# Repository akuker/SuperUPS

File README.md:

# Supercapacitor UPS board for Raspberry Pi

This is a fork of the original Supercapacitor UPS board for a Raspberry Pi by Scott Baker, http://www.smbaker.com/

This fork is intended to improve producability, documentation and provide tighter integration with the RaSCSI project. This project does NOT require a RaSCSI to function.

See [SETUP.md](SETUP.md) for setup instructions

## Very early 3D renderings

## Why not other Supercapacitor designs?

Most of the existing Raspberry Pi UPS designs rely on GPIO pins to alert the Raspberry Pi of a power loss. The RaSCSI design makes heavy usage of the GPIO pins, so there are not sufficient spare to allow this. This design will utilize a microcontroller to manage the power and allow the Rapsberry Pi to read the status through I2C.

# Purpose

These boards are supercapacitor-based uninterruptable power supplies. The supercapacitor charges when power is applied, then when the power supply is terminated, the supercapacitor will operate the device long enough for it to shut down safely.

# Design - 12V board (5v output)

The 12V board uses five 2.7V supercapacitors in series, with 2.7V shunt regulators to ensure that no single capacitor is charged to more than 2.5 volts. A 3W resistor is used to limit the current that charges the capacitors. A jumper is provided to allow the capacitors to be rapid discharged. A mosfet is added to allow the load to be turned on/off.

Note: Scott Baker's original design also included a version of the UPS board that took a 5v input. This fork is focusing on the 12v version and will not include the 5v input version.

# Microcontroller manager

~~An ATTiny85 is used as the controller for the UPS.~~ *Now a STM8 due to the parts shortages.* The microcontroller monitors the battery voltage and the incoming voltage, and switches the load on and off. The microcontroller supports I2C and can be interfaced directly to a raspberry pi.

The microcontroller is also responsible for noticing when power has been restored, and turning the load back on.

[Design Overview](docs/microcontroller_design.md)

# Linux Daemon

A Linux daemon, running on the raspberry pi, monitors the voltage by making i2c queries to the ups board's microcontroller. If the daemon sees the incoming voltage drop, then it will initiate shutdown, by running the `shutdown` command. The shutdown command will terminate processes, unmount the filesystem, etc. 

~~As a final step during shutdown, Linux systemd will execute a script that will tell the microcontroller to turn off the load. At this point, the root filesystem has been remounted readonly, so the board can safely be powered off. ~~

# ~~smb-pi-lib~~

~~Scott Baker has a second repository that has common code for a number of my projects, including the ups. It's located at [https://github.com/sbelectronics/smb-pi-lib](https://github.com/sbelectronics/smb-pi-lib)~~

# Acknowledgements

* Scott Baker for doing a fantastic supercapcitor based UPS design.
* David Gesswein's MFM Emulator was the inspiration for the supercapacitor charing circuit.

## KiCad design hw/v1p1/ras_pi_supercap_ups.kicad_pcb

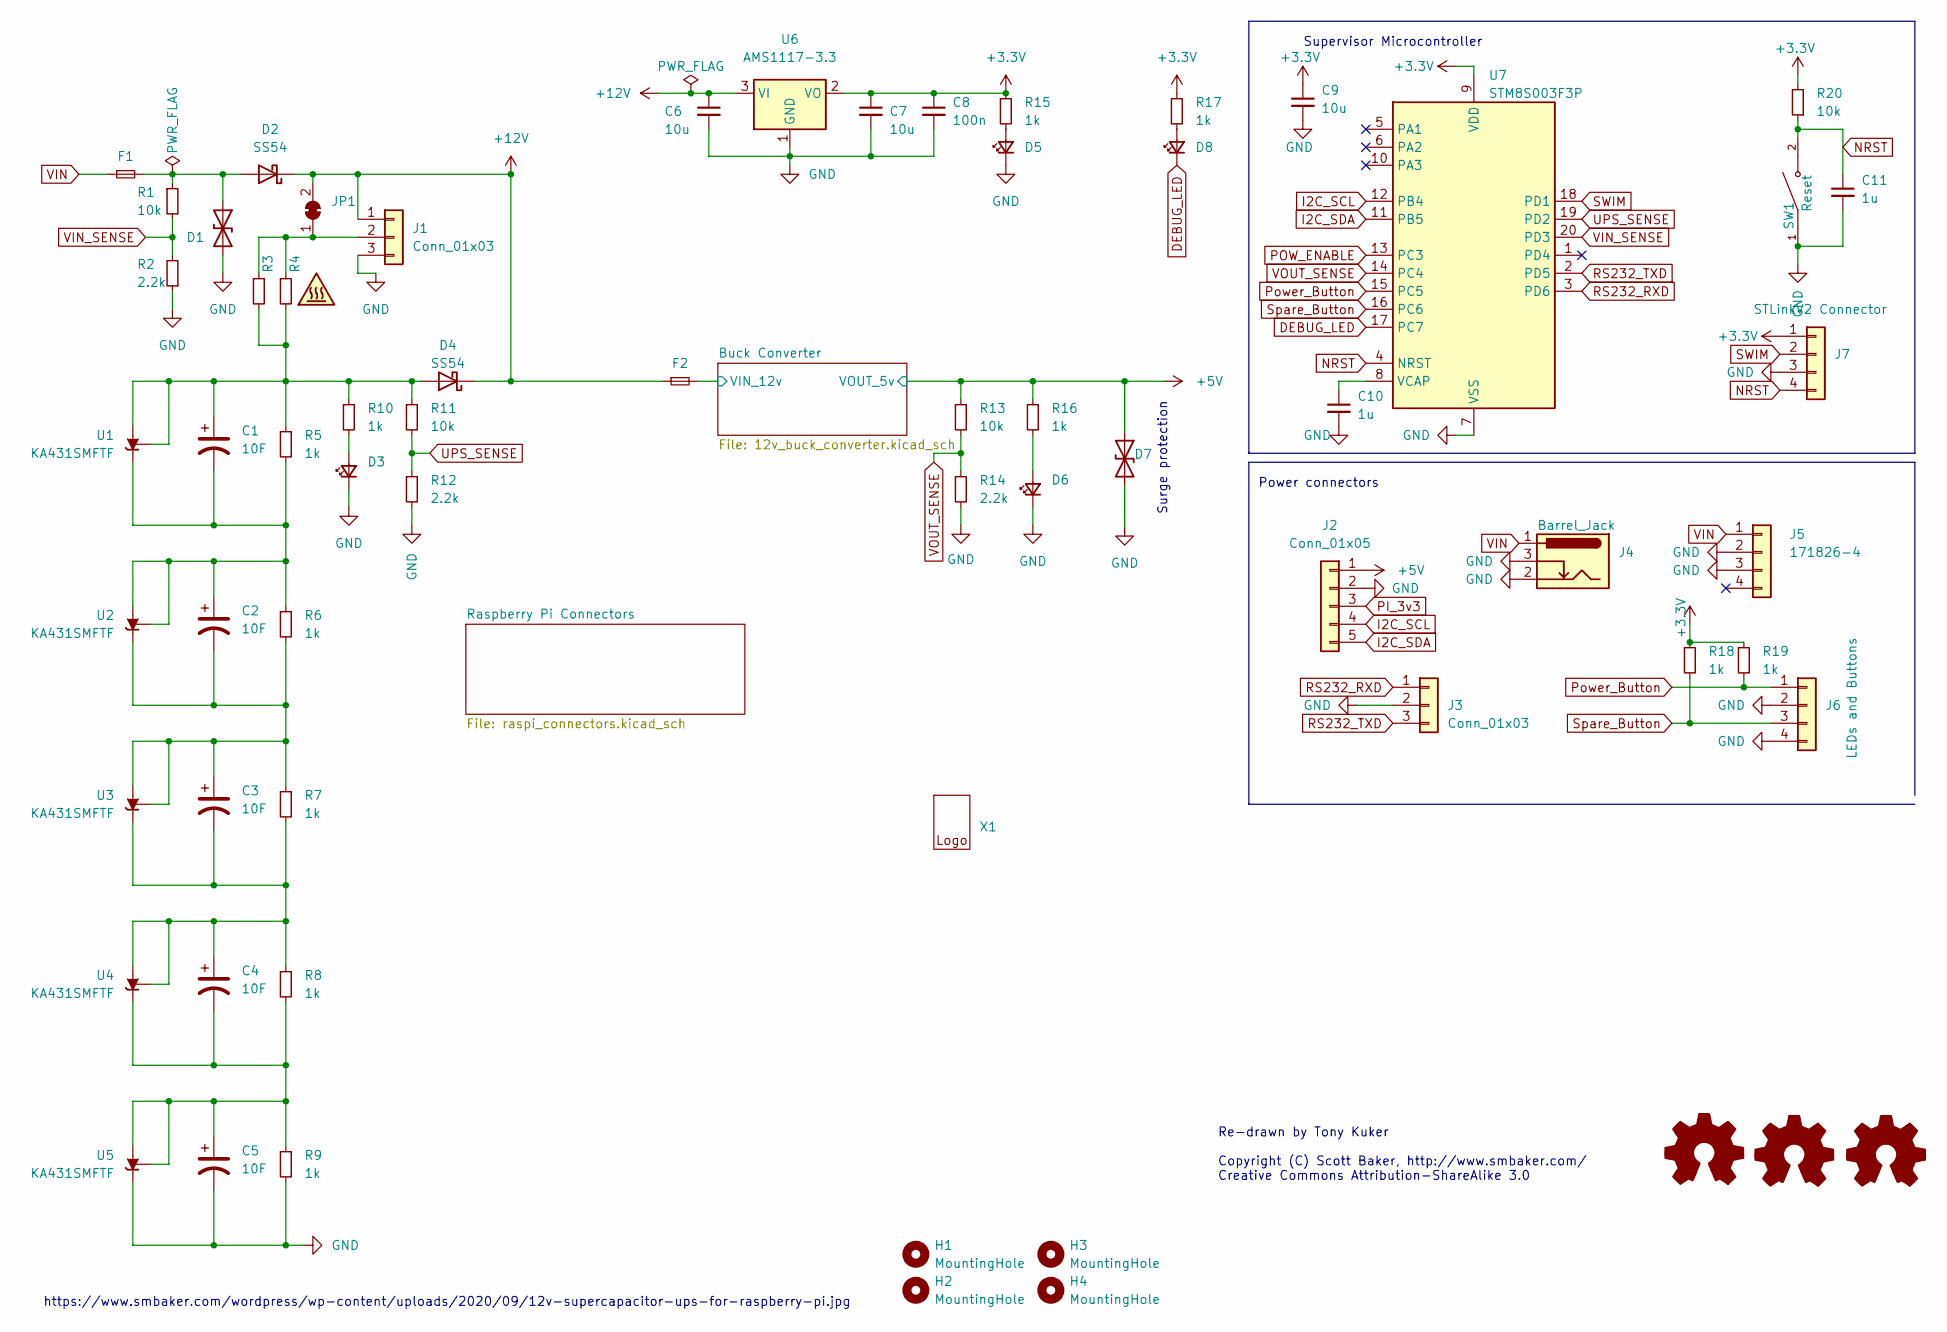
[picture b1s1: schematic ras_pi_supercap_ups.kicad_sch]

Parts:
C1, C2, C3, C4, C5: 10F; CP_Radial_D10.0mm_P5.00mm; DigikeyPN 478-10996-ND
C6, C7, C9: 10u; C_0805_2012Metric; DigikeyPN 445-FK26X7R1E106K-ND
C8: 100n; C_0805_2012Metric; LCSC C28233
C10, C11: 1u; C_0805_2012Metric; LCSC C28323
D1, D7: PTVSHC3D15VUH; D_SOD-323; LCSC C312234
D2, D4: SS54; D_SMA; LCSC C22452
D3, D5, D6, D8: Green; LED_0805_2012Metric; LCSC C2297
F1, F2: Fuse_Small; Fuse_1206_3216Metric; LCSC C140470
H1, H2, H3, H4: MountingHole; MountingHole_2.7mm_M2.5; LCSC DNP
J1: Conn_01x03; PinHeader_1x03_P2.54mm_Vertical; DigikeyPN NA
J2: Conn_01x05; PinHeader_1x05_P2.54mm_Vertical; DigikeyPN NA
J3: Conn_01x03; PinHeader_1x03_P2.54mm_Vertical; DigikeyPN A106204-ND
J4: Barrel_Jack; BarrelJack_Wuerth_6941xx301002; LCSC C521451
J5: 171826-4; TE_171826-4; LCSC DNP
J6: LEDs and Buttons; PinHeader_1x04_P2.54mm_Vertical; LCSC DNP
J7: STLinkV2 Connector; PinHeader_1x04_P2.54mm_Vertical
JP1: Charge Enb; SolderJumper-2_P1.3mm_Bridged_RoundedPad1.0x1.5mm
R1, R11, R13, R20: 10k; R_0805_2012Metric; DigikeyPN CF14JT10K0CT-ND
R2, R12, R14: 2.2k; R_0805_2012Metric; DigikeyPN CF14JT2K20TR-ND
R3, R4: 10 3W; SMT_Resistor_4122; DigikeyPN YAG1228CT-ND
R5, R6, R7, R8, R9: 1k; R_1206_3216Metric; DigikeyPN CF14JT1K00CT-ND
R10, R15, R16, R17, R18, R19: 1k; R_0805_2012Metric; DigikeyPN CF14JT1K00CT-ND
SW1: Reset; SW_TS-1187A-B-A-B; PARTREV A0; LCSC C318884
U1, U2, U3, U4, U5: KA431SMFTF; SOT-23; LCSC C3113
U6: AMS1117-3.3; SOT-223-3_TabPin2; LCSC C6186
U7: STM8S003F3P; TSSOP-20_4.4x6.5mm_P0.65mm; LCSC C52717
X1: Polarity_Center_Positive_6mm_SilkScreen
Z1: SYM_Hot_Small; hot_warning_4
Z2: Logo_Open_Hardware_Small; OSHW-Logo_7.5x8mm_SilkScreen
Z3: Logo_Open_Hardware_Small; CE-Logo_8.5x6mm_SilkScreen
Z4: Logo_Open_Hardware_Small; KiCad-Logo_5mm_Copper

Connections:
+3.3V: C7.1, C8.1, C9.1, J7.1, R15.1, R17.1, R18.1, R19.1, R20.2, U6.2 (VO), U7.9 (VDD)
+5V: D7.1 (A1), J2.1, R13.1, R16.1; also elsewhere on the board
+12V: C6.1, D2.1 (K), D4.1 (K), F2.1, J1.1, JP1.2 (B), U6.3 (VI)
/Buck Converter/VIN_12v: F2.2; also elsewhere on the board
DEBUG_LED: D8.1 (K), U7.17 (PC7)
GND: C5.2, C6.2, C7.2, C8.2, C9.2, C10.2, C11.2, D1.2 (A2), D3.1 (K), D5.1 (K), D6.1 (K), D7.2 (A2), J1.3, J2.2, J3.2, J4.2, J4.3, J5.2, J5.3, J6.2, J6.4, J7.3, R2.1, R9.2, R12.2, R14.2, SW1.1, U5.2 (K), U6.1 (GND), U7.7 (VSS); also elsewhere on the board
I2C_SCL: J2.4, U7.12 (PB4); also elsewhere on the board
I2C_SDA: J2.5, U7.11 (PB5); also elsewhere on the board
NRST: C11.1, J7.4, R20.1, SW1.2, U7.4 (NRST)
unnamed: D1.1 (A1), D2.2 (A), F1.2, R1.1
unnamed: D3.2 (A), R10.2
unnamed: C1.1, D4.2 (A), R3.2, R4.2, R5.1, R10.1, R11.1, U1.1 (REF), U1.3 (A)
unnamed: D5.2 (A), R15.2
unnamed: D6.2 (A), R16.2
unnamed: D8.2 (A), R17.2
unnamed: J1.2, JP1.1 (A), R3.1, R4.1
unnamed: C1.2, C2.1, R5.2, R6.1, U1.2 (K), U2.1 (REF), U2.3 (A)
unnamed: C2.2, C3.1, R6.2, R7.1, U2.2 (K), U3.1 (REF), U3.3 (A)
unnamed: C3.2, C4.1, R7.2, R8.1, U3.2 (K), U4.1 (REF), U4.3 (A)
unnamed: C4.2, C5.1, R8.2, R9.1, U4.2 (K), U5.1 (REF), U5.3 (A)
unnamed: C10.1, U7.8 (VCAP)
PI_3v3: J2.3; also elsewhere on the board
POW_ENABLE: U7.13 (PC3); also elsewhere on the board
Power_Button: J6.1, R19.2, U7.15 (PC5)
RS232_RXD: J3.1, U7.3 (PD6)
RS232_TXD: J3.3, U7.2 (PD5)
SWIM: J7.2, U7.18 (PD1)
Spare_Button: J6.3, R18.2, U7.16 (PC6)
UPS_SENSE: R11.2, R12.1, U7.19 (PD2)
VIN: F1.1, J4.1, J5.1
VIN_SENSE: R1.2, R2.2, U7.20 (PD3)
VOUT_SENSE: R13.2, R14.1, U7.14 (PC4)

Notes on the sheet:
https://www.smbaker.com/wordpress/wp-content/uploads/2020/09/12v-supercapacitor-ups-for-raspberry-pi.jpg
Power connectors
Re-drawn by Tony Kuker Copyright (C) Scott Baker, http://www.smbaker.com/ Creative Commons Attribution-ShareAlike 3.0
Surge protection
Supervisor Microcontroller

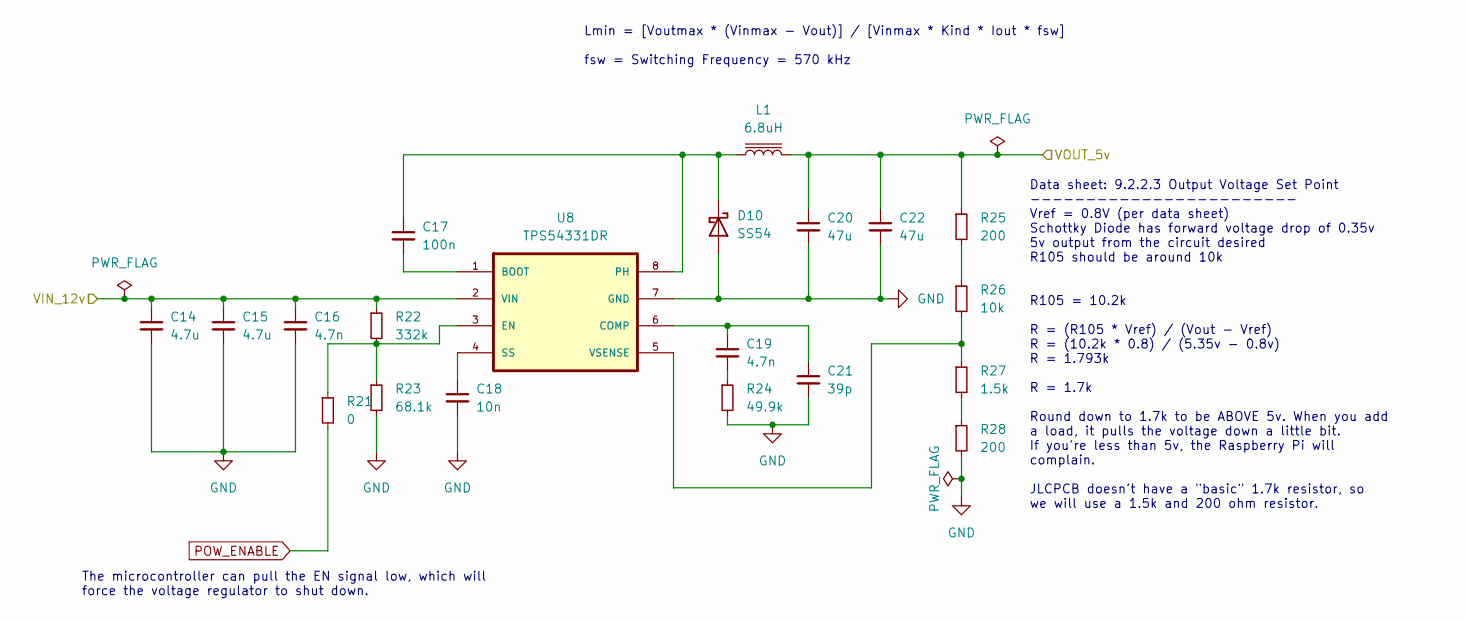
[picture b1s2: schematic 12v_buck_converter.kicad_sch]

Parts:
C14, C15: 4.7u; C_0805_2012Metric; LCSC C1779
C16, C19: 4.7n; C_0805_2012Metric; LCSC C1744
C17: 100n; C_0805_2012Metric; LCSC C28233
C18: 10n; C_0805_2012Metric; LCSC C1710
C20, C22: 47u; C_0805_2012Metric; LCSC C16780
C21: 39p; C_0805_2012Metric; LCSC C296098
D10: SS54; D_SMA; LCSC C22452
L1: 6.8uH; Sunltech_SLO0530H; LCSC C325965
R21: 0; R_0805_2012Metric; DigikeyPN CF14JT1K00CT-ND
R22: 332k; R_0805_2012Metric; LCSC C17631
R23: 68.1k; R_0805_2012Metric; LCSC C17795
R24: 49.9k; R_0805_2012Metric; LCSC C17719
R25: 200; R_0805_2012Metric; LCSC C17540
R26: 10k; R_0805_2012Metric; LCSC C17414
R27: 1.5k; R_0805_2012Metric; LCSC C4310
R28: 200; R_0805_2012Metric; LCSC C17557
U8: TPS54331DR; SOIC127P599X175-8N; LCSC C9865

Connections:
+5V: C20.1, C22.1, L1.2, R25.1; also elsewhere on the board
/Buck Converter/VIN_12v: C14.1, C15.1, C16.1, R22.1, U8.2 (VIN); also elsewhere on the board
GND: C14.2, C15.2, C16.2, C18.2, C20.2, C21.2, C22.2, D10.2 (A), R23.2, R24.2, R28.2, U8.7 (GND); also elsewhere on the board
unnamed: C19.2, R24.1
unnamed: C17.1, D10.1 (K), L1.1, U8.8 (PH)
unnamed: R25.2, R26.1
unnamed: R27.2, R28.1
unnamed: C17.2, U8.1 (BOOT)
unnamed: C19.1, C21.1, U8.6 (COMP)
unnamed: R21.1, R22.2, R23.1, U8.3 (EN)
unnamed: C18.1, U8.4 (SS)
unnamed: R26.2, R27.1, U8.5 (VSENSE)
POW_ENABLE: R21.2; also elsewhere on the board

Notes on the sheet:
The microcontroller can pull the EN signal low, which will force the voltage regulator to shut down.
Data sheet: 9.2.2.3 Output Voltage Set Point ------------------------ Vref = 0.8V (per data sheet) Schottky Diode has forward voltage drop of 0.35v 5v output from the circuit desired R105 should be around 10k R105 = 10.2k R = (R105 * Vref) / (Vout - Vref) R = (10.2k * 0.8) / (5.35v - 0.8v) R = 1.79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
Lmin = [Voutmax * (Vinmax - Vout)] / [Vinmax * Kind * Iout * fsw] fsw = Switching Frequency = 570 kHz

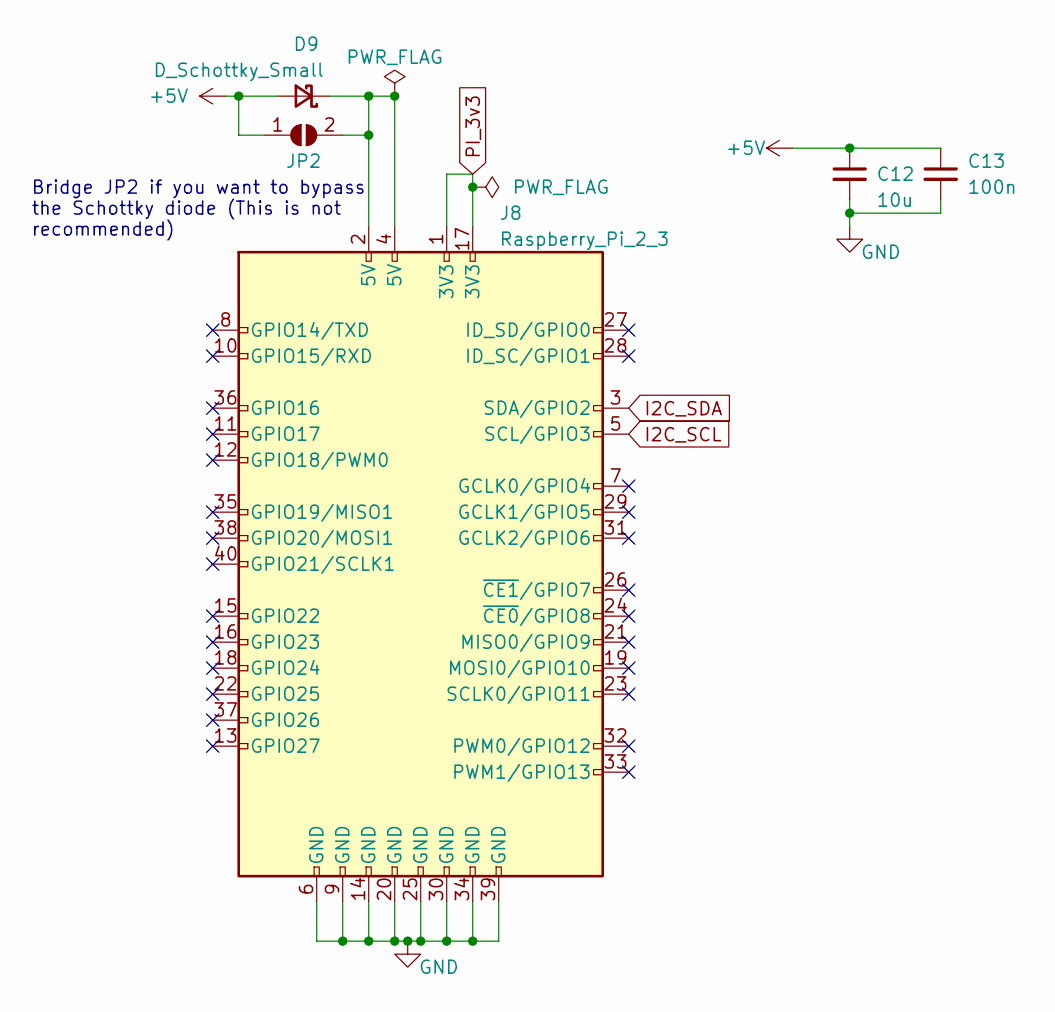
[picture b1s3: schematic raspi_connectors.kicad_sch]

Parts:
C12: 10u; C_0805_2012Metric; DigikeyPN 445-FK26X7R1E106K-ND
C13: 100n; C_0805_2012Metric; LCSC C28233
D9: D_Schottky_Small; D_SMA; LCSC C8678
J8: Raspberry_Pi_2_3; PinSocket_2x20_P2.54mm_Vertical; LCSC DNP
JP2: SolderJumper_2_Open; SolderJumper-2_P1.3mm_Open_RoundedPad1.0x1.5mm

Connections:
+5V: C12.1, C13.1, D9.2 (A), JP2.1 (A); also elsewhere on the board
GND: C12.2, C13.2, J8.6 (GND), J8.9 (GND), J8.14 (GND), J8.20 (GND), J8.25 (GND), J8.30 (GND), J8.34 (GND), J8.39 (GND); also elsewhere on the board
I2C_SCL: J8.5 (SCL/GPIO3); also elsewhere on the board
I2C_SDA: J8.3 (SDA/GPIO2); also elsewhere on the board
unnamed: D9.1 (K), J8.2 (5V), J8.4 (5V), JP2.2 (B)
PI_3v3: J8.1 (3V3), J8.17 (3V3); also elsewhere on the board

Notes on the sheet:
Bridge JP2 if you want to bypass the Schottky diode (This is not recommended)

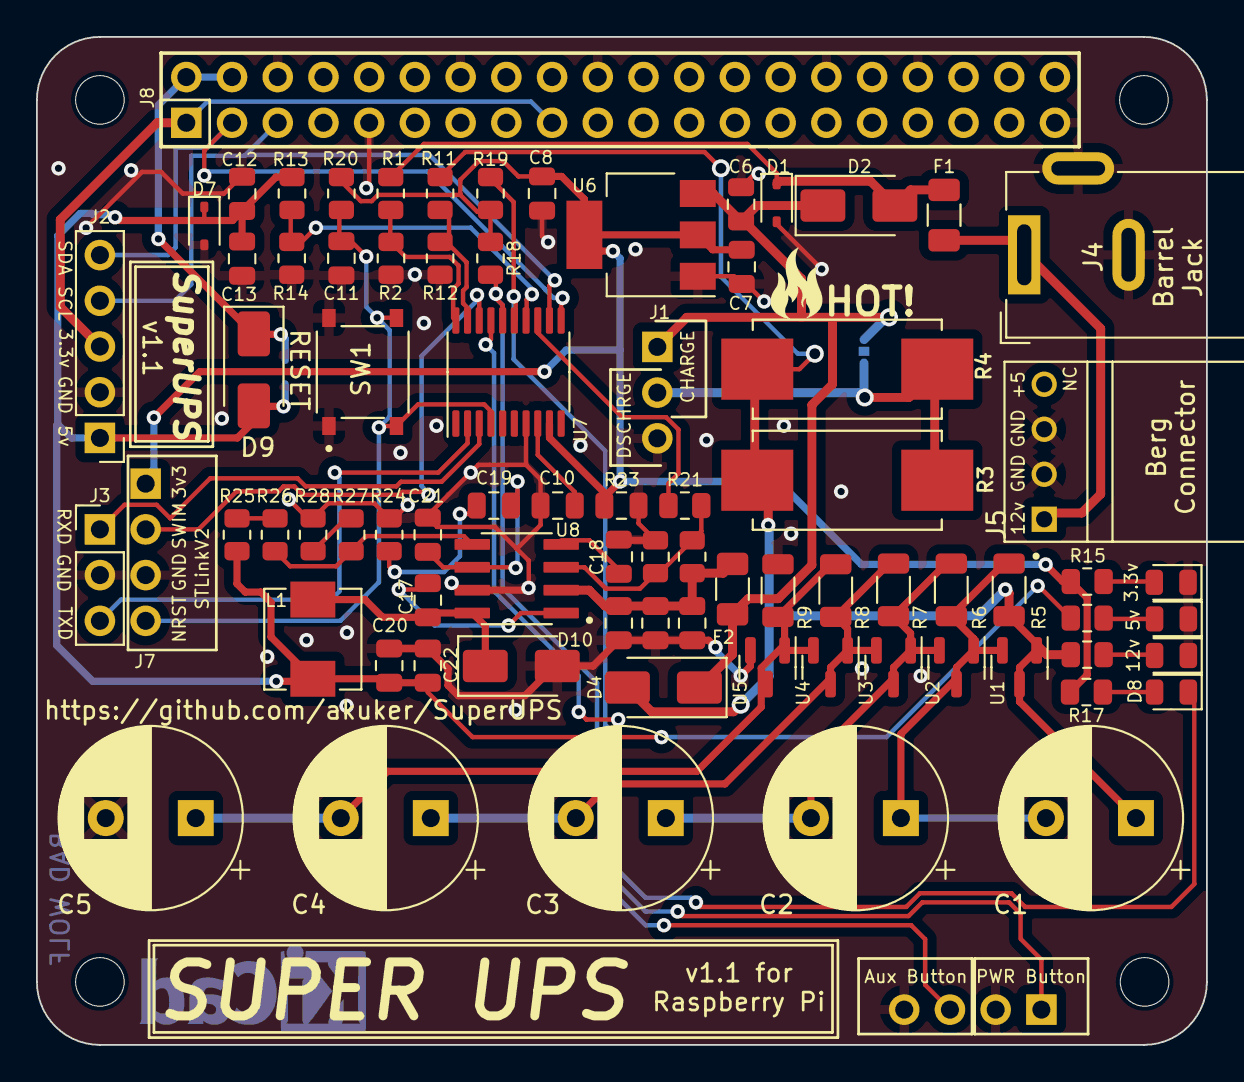
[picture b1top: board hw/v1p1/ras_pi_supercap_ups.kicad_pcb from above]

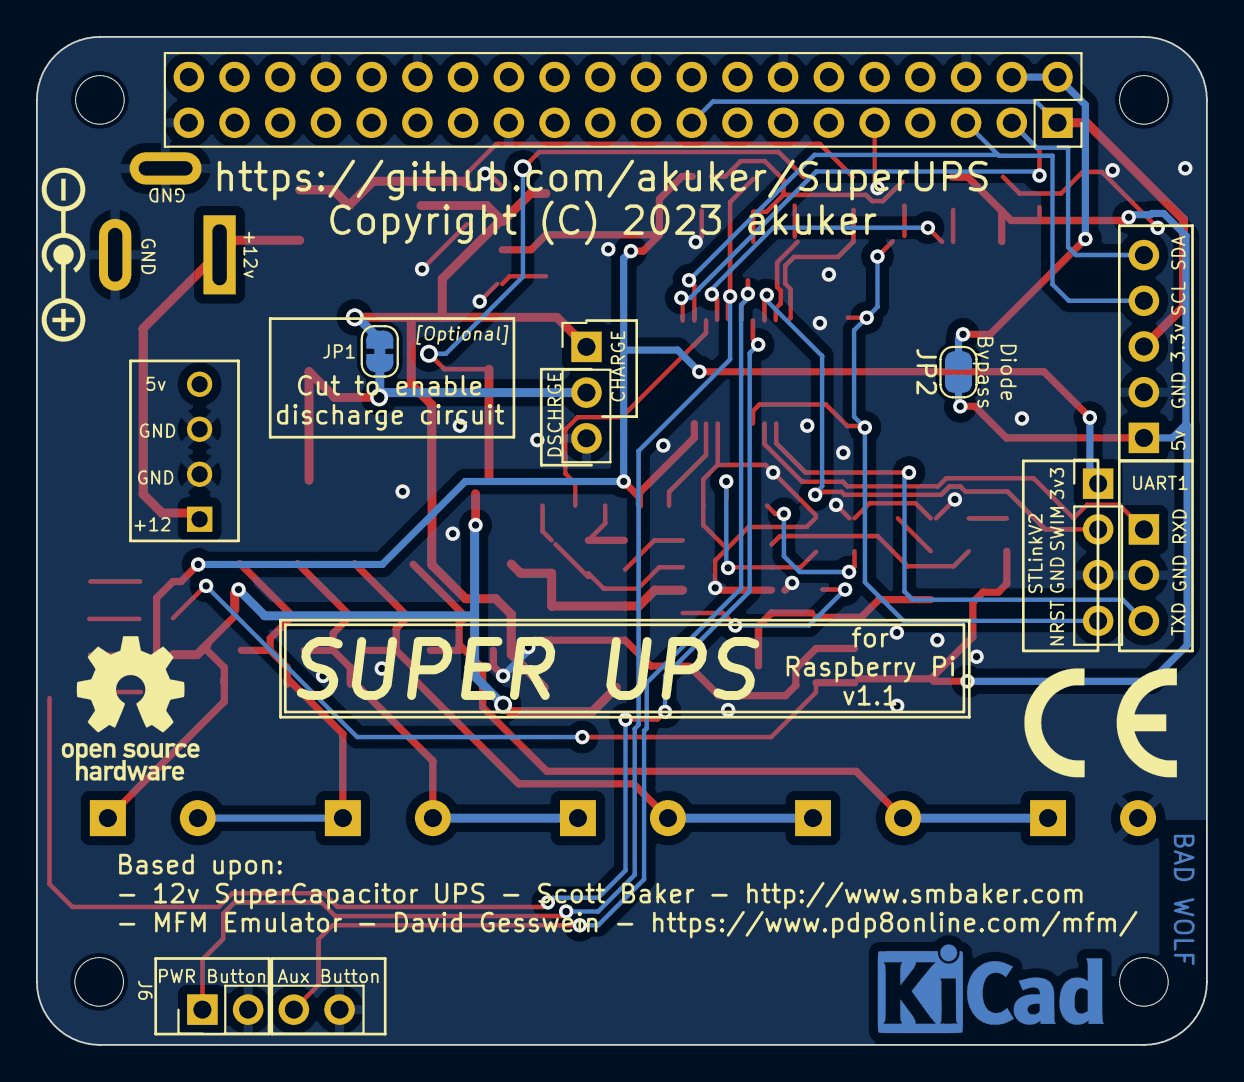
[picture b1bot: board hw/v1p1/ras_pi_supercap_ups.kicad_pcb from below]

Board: 2 copper layers, 65.0 x 56.0 mm, 91 parts (10 on the bottom side), 42 nets.

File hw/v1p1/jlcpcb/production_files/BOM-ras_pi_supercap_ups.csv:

Comment,Designator,Footprint,LCSC
Fuse_Small,"F1,F2",Fuse_1206_3216Metric,C140470
10u,"C12,C6,C7,C9",C_0805_2012Metric,C15850
47u,"C20,C22",C_0805_2012Metric,C16780
10n,C18,C_0805_2012Metric,C1710
10k,"R1,R11,R13,R20,R26",R_0805_2012Metric,C17414
4.7n,"C16,C19",C_0805_2012Metric,C1744
0,R21,R_0805_2012Metric,C17477
1k,"R10,R15,R16,R17,R18,R19",R_0805_2012Metric,C17513
2.2k,"R12,R14,R2",R_0805_2012Metric,C17520
200,R25,R_0805_2012Metric,C17540
200,R28,R_0805_2012Metric,C17557
332k,R22,R_0805_2012Metric,C17631
49.9k,R24,R_0805_2012Metric,C17719
4.7u,"C14,C15",C_0805_2012Metric,C1779
68.1k,R23,R_0805_2012Metric,C17795
SS54,"D10,D2,D4",D_SMA,C22452
Green,"D3,D5,D6,D8",LED_0805_2012Metric,C2297
100n,"C13,C17,C8",C_0805_2012Metric,C28233
1u,"C10,C11",C_0805_2012Metric,C28323
39p,C21,C_0805_2012Metric,C296098
10 3W,"R3,R4",SMT_Resistor_4122,C306270
KA431SMFTF,"U1,U2,U3,U4,U5",SOT-23,C3113
PTVSHC3D15VUH,"D1,D7",D_SOD-323,C312234
Reset,SW1,SW_TS-1187A-B-A-B,C318884
6.8uH,L1,Sunltech_SLO0530H,C325965
1.5k,R27,R_0805_2012Metric,C4310
1k,"R5,R6,R7,R8,R9",R_1206_3216Metric,C4410
Barrel_Jack,J4,BarrelJack_Wuerth_6941xx301002,C521451
STM8S003F3P,U7,TSSOP-20_4.4x6.5mm_P0.65mm,C52717
AMS1117-3.3,U6,SOT-223-3_TabPin2,C6186
D_Schottky_Small,D9,D_SMA,C8678
TPS54331DR,U8,SOIC127P599X175-8N,C9865
10F,C3,CP_Radial_D10.0mm_P5.00mm,
171826-4,J5,TE_171826-4,
10F,C1,CP_Radial_D10.0mm_P5.00mm,
MountingHole,H1,MountingHole_2.7mm_M2.5,
MountingHole,H2,MountingHole_2.7mm_M2.5,
MountingHole,H4,MountingHole_2.7mm_M2.5,
10F,C5,CP_Radial_D10.0mm_P5.00mm,
MountingHole,H3,MountingHole_2.7mm_M2.5,
10F,C4,CP_Radial_D10.0mm_P5.00mm,
Conn_01x03,J3,PinHeader_1x03_P2.54mm_Vertical,
Conn_01x05,J2,PinHeader_1x05_P2.54mm_Vertical,
10F,C2,CP_Radial_D10.0mm_P5.00mm,
SolderJumper_2_Open,JP2,SolderJumper-2_P1.3mm_Open_RoundedPad1.0x1.5mm,
Charge Enb,JP1,SolderJumper-2_P1.3mm_Bridged_RoundedPad1.0x1.5mm,
LEDs and Buttons,J6,PinHeader_1x04_P2.54mm_Vertical,
Logo_Open_Hardware_Small,Z3,CE-Logo_8.5x6mm_SilkScreen,
Raspberry_Pi_2_3,J8,PinSocket_2x20_P2.54mm_Vertical,
Logo_Open_Hardware_Small,Z2,OSHW-Logo_7.5x8mm_SilkScreen,
STLinkV2 Connector,J7,PinHeader_1x04_P2.54mm_Vertical,
Conn_01x03,J1,PinHeader_1x03_P2.54mm_Vertical,

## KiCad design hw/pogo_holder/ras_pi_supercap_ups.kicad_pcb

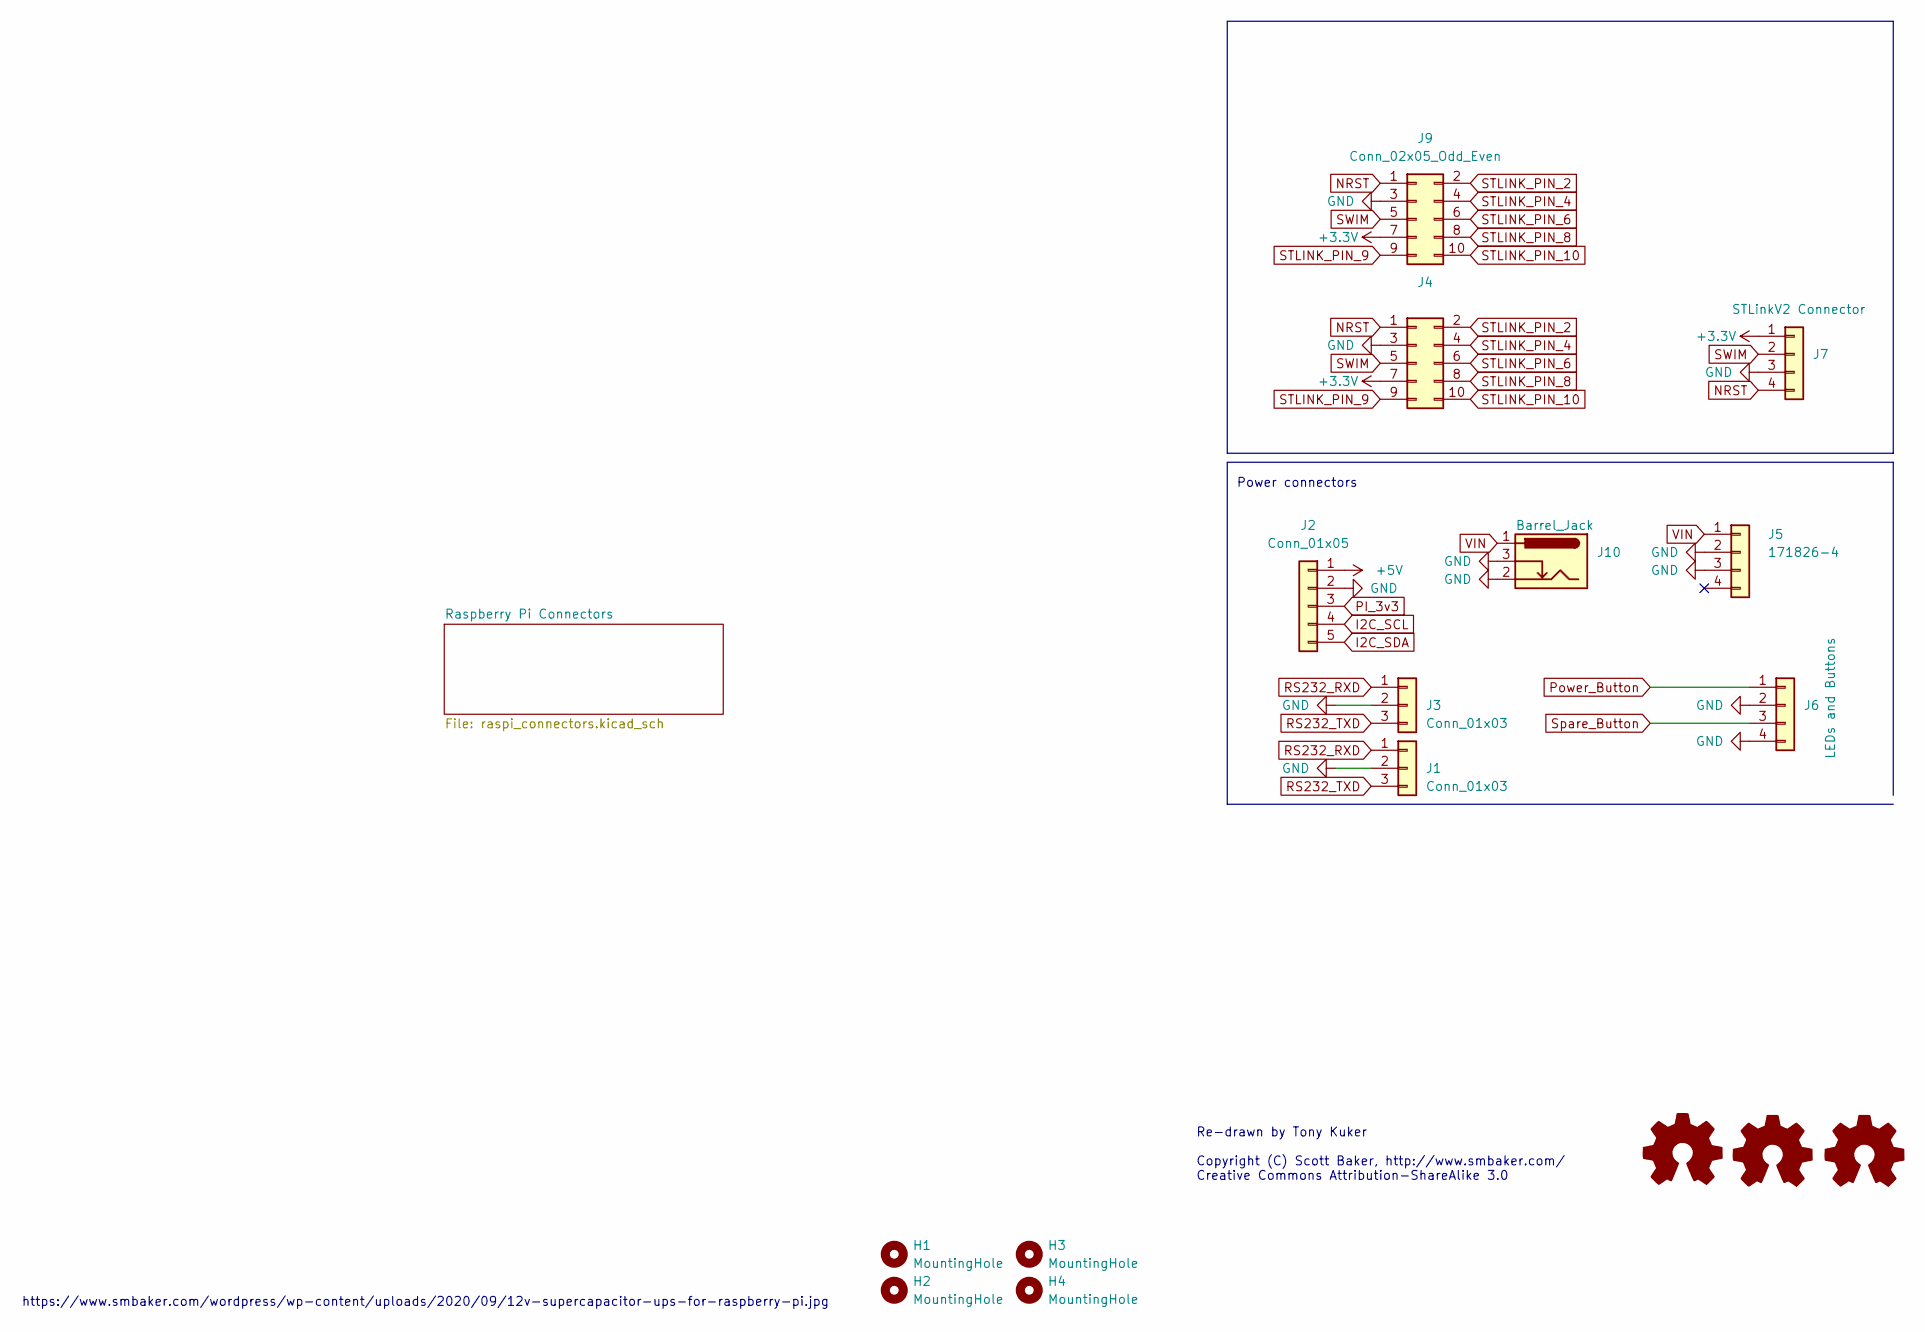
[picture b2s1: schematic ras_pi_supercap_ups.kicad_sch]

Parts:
H1, H2, H3, H4: MountingHole; MountingHole_2.7mm_M2.5; LCSC DNP
J1, J3: Conn_01x03; PinHeader_1x03_P2.54mm_Vertical; DigikeyPN A106204-ND
J2: Conn_01x05; PinHeader_1x05_P2.54mm_Vertical; DigikeyPN NA
J4: (no value)
J5: 171826-4; TE_171826-4; LCSC DNP
J6: LEDs and Buttons; PinHeader_1x04_P2.54mm_Vertical; LCSC DNP
J7: STLinkV2 Connector; PinHeader_1x04_P2.54mm_Vertical
J9: Conn_02x05_Odd_Even; PinHeader_2x05_P2.54mm_Vertical
J10: Barrel_Jack; BarrelJack_Wuerth_6941xx301002; LCSC C521451
Z2: Logo_Open_Hardware_Small; CE-Logo_8.5x6mm_SilkScreen
Z3: Logo_Open_Hardware_Small; KiCad-Logo_5mm_Copper
Z4: Logo_Open_Hardware_Small; OSHW-Logo_7.5x8mm_SilkScreen

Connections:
+3V3: J4.7, J7.1, J9.7
+5V: J2.1
GND: J1.2, J2.2, J3.2, J4.3, J5.2, J5.3, J6.2, J6.4, J7.3, J9.3, J10.2, J10.3; also elsewhere on the board
I2C_SCL: J2.4; also elsewhere on the board
I2C_SDA: J2.5; also elsewhere on the board
NRST: J4.1, J7.4, J9.1
PI_3v3: J2.3
Power_Button: J6.1
RS232_RXD: J1.1, J3.1
RS232_TXD: J1.3, J3.3
STLINK_PIN_2: J4.2, J9.2
STLINK_PIN_4: J4.4, J9.4
STLINK_PIN_6: J4.6, J9.6
STLINK_PIN_8: J4.8, J9.8
STLINK_PIN_9: J4.9, J9.9
STLINK_PIN_10: J4.10, J9.10
SWIM: J4.5, J7.2, J9.5
Spare_Button: J6.3
VIN: J5.1, J10.1

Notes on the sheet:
https://www.smbaker.com/wordpress/wp-content/uploads/2020/09/12v-supercapacitor-ups-for-raspberry-pi.jpg
Power connectors
Re-drawn by Tony Kuker Copyright (C) Scott Baker, http://www.smbaker.com/ Creative Commons Attribution-ShareAlike 3.0

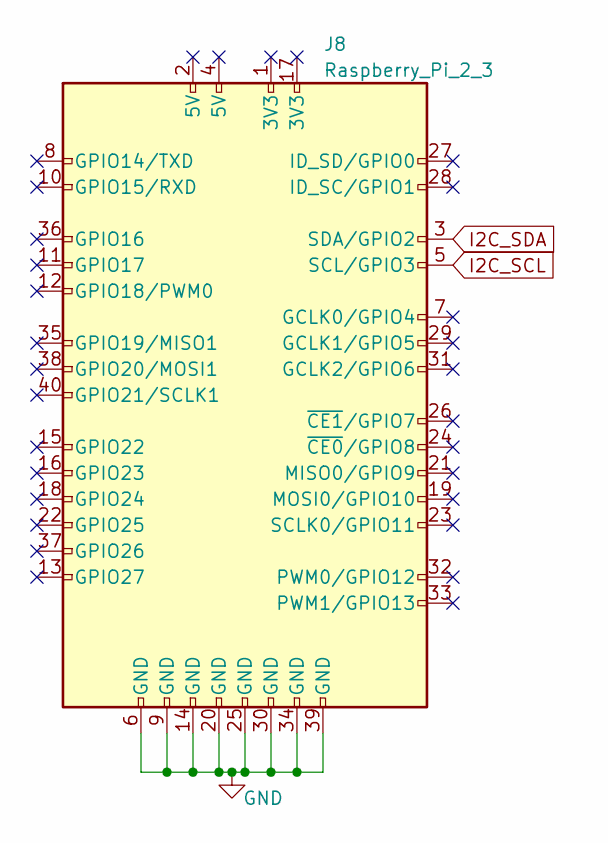
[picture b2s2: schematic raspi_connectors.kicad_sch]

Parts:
J8: Raspberry_Pi_2_3; PinSocket_2x20_P2.54mm_Vertical; LCSC DNP

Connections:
GND: J8.6 (GND), J8.9 (GND), J8.14 (GND), J8.20 (GND), J8.25 (GND), J8.30 (GND), J8.34 (GND), J8.39 (GND); also elsewhere on the board
I2C_SCL: J8.5 (SCL/GPIO3); also elsewhere on the board
I2C_SDA: J8.3 (SDA/GPIO2); also elsewhere on the board

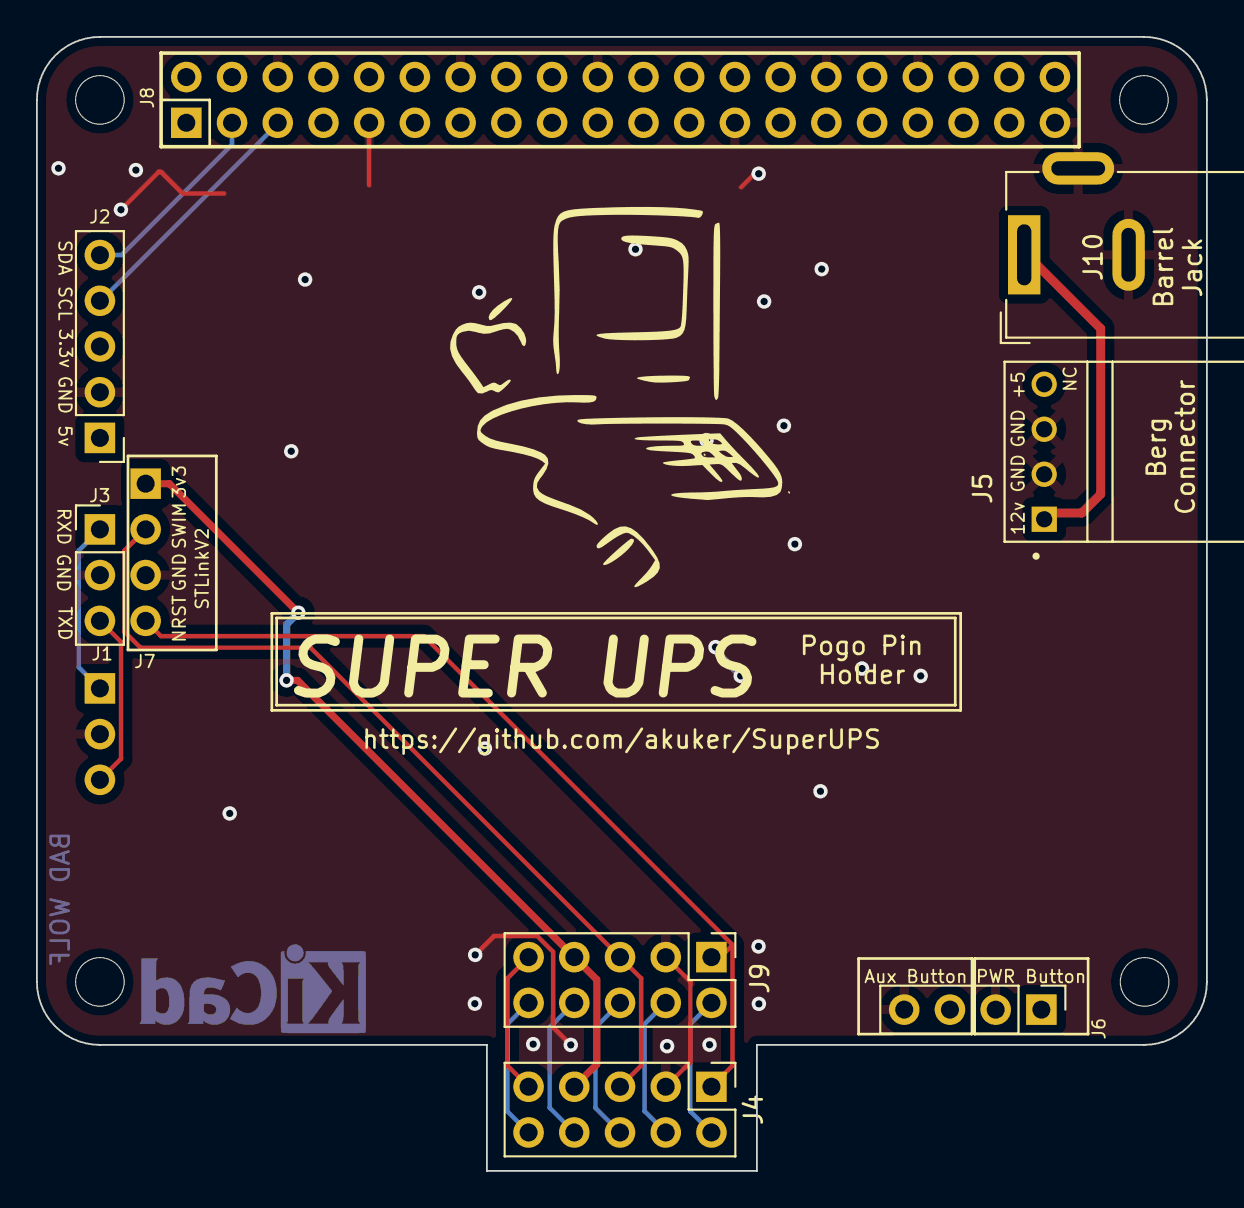
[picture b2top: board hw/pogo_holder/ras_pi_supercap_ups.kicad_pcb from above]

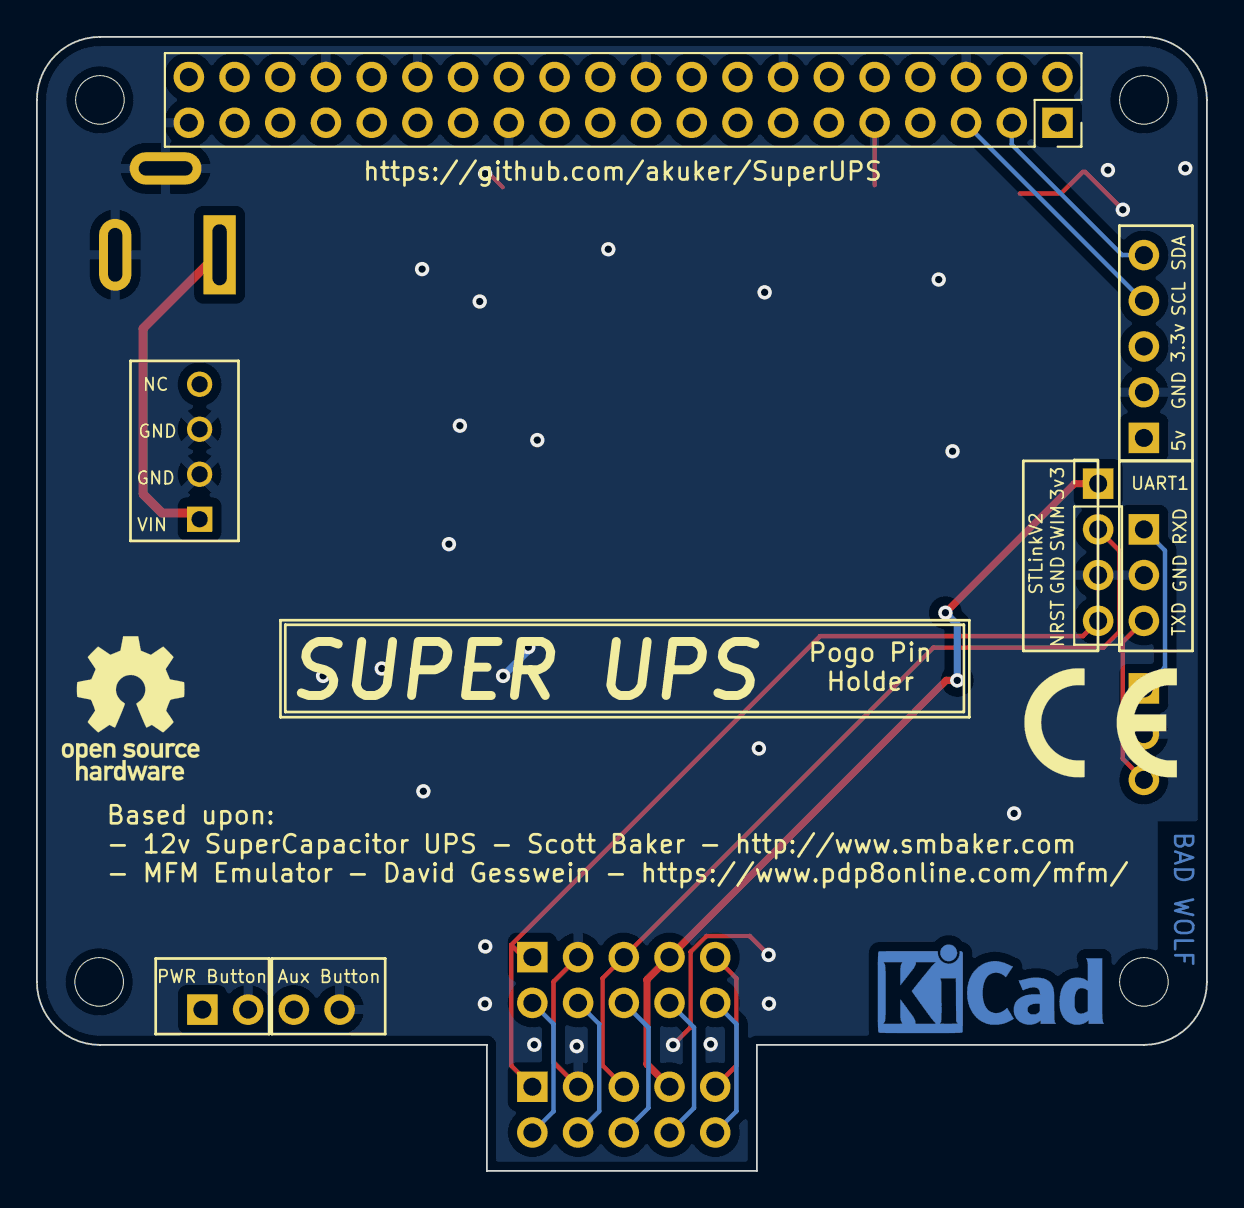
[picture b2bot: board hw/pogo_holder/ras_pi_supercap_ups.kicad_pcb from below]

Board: 2 copper layers, 65.0 x 63.0 mm, 17 parts (6 on the bottom side), 15 nets.

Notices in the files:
hw/v1p1/ras_pi_supercap_ups.kicad_pcb:
Copyright (C) 2023 akuker
